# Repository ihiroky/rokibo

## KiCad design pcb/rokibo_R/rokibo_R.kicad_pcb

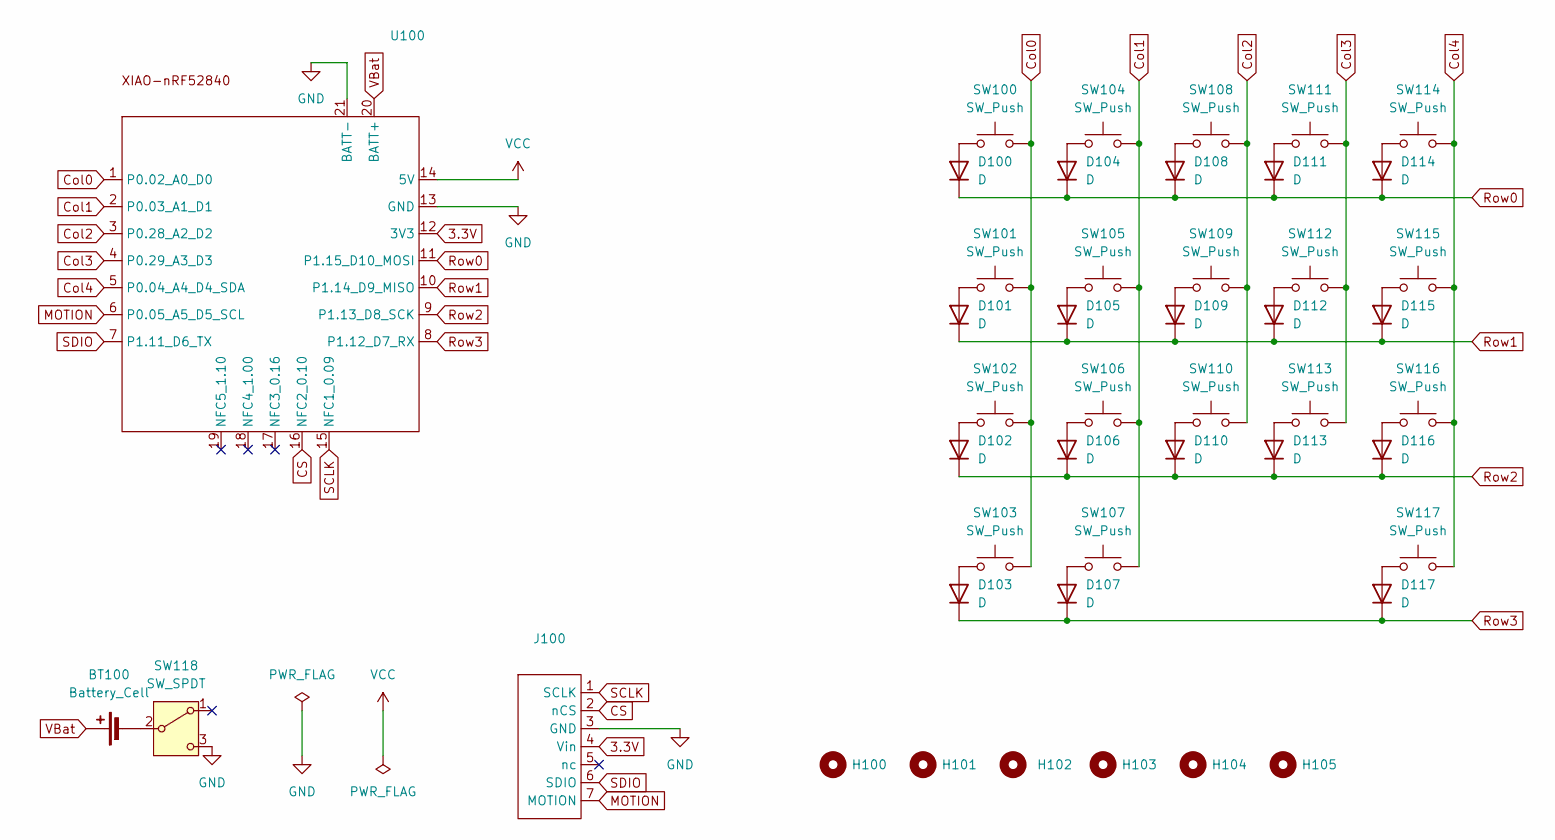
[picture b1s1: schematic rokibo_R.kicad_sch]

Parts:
BT100: Battery_Cell; JST_S2B-PH-SM4-TB
D100, D101, D102, D103, D104, D105, D106, D107, D108, D109, D110, D111, D112, D113, D114, D115, D116, D117: D; Diode_SMD
H100, H101, H102, H103, H104, H105: m2_Spacer_Hole
J100: pmw3610_connector
SW100, SW101, SW102, SW103, SW104, SW105, SW106, SW107, SW108, SW109, SW110, SW111, SW112, SW113, SW114, SW115, SW116, SW117: SW_Push; SW_MX_Choc_THCS
SW118: SW_SPDT; TGSW_MSK-12D19
U100: XIAO_nRF52840_wBAT_wNFC_1

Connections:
3.3V: J100.4 (Vin), U100.12 (3V3)
CS: J100.2 (nCS), U100.16 (NFC2_0.10)
Col0: SW100.2, SW101.2, SW102.2, SW103.2, U100.1 (P0.02_A0_D0)
Col1: SW104.2, SW105.2, SW106.2, SW107.2, U100.2 (P0.03_A1_D1)
Col2: SW108.2, SW109.2, SW110.2, U100.3 (P0.28_A2_D2)
Col3: SW111.2, SW112.2, SW113.2, U100.4 (P0.29_A3_D3)
Col4: SW114.2, SW115.2, SW116.2, SW117.2, U100.5 (P0.04_A4_D4_SDA)
GND: J100.3 (GND), SW118.3 (C), U100.13 (GND), U100.21 (BATT-)
MOTION: J100.7 (MOTION), U100.6 (P0.05_A5_D5_SCL)
unnamed: BT100.2 (-), SW118.2 (B)
unnamed: D100.2 (A), SW100.1
unnamed: D101.2 (A), SW101.1
unnamed: D102.2 (A), SW102.1
unnamed: D103.2 (A), SW103.1
unnamed: D104.2 (A), SW104.1
unnamed: D105.2 (A), SW105.1
unnamed: D106.2 (A), SW106.1
unnamed: D107.2 (A), SW107.1
unnamed: D108.2 (A), SW108.1
unnamed: D109.2 (A), SW109.1
unnamed: D110.2 (A), SW110.1
unnamed: D111.2 (A), SW111.1
unnamed: D112.2 (A), SW112.1
unnamed: D113.2 (A), SW113.1
unnamed: D114.2 (A), SW114.1
unnamed: D115.2 (A), SW115.1
unnamed: D116.2 (A), SW116.1
unnamed: D117.2 (A), SW117.1
Row0: D100.1 (K), D104.1 (K), D108.1 (K), D111.1 (K), D114.1 (K), U100.11 (P1.15_D10_MOSI)
Row1: D101.1 (K), D105.1 (K), D109.1 (K), D112.1 (K), D115.1 (K), U100.10 (P1.14_D9_MISO)
Row2: D102.1 (K), D106.1 (K), D110.1 (K), D113.1 (K), D116.1 (K), U100.9 (P1.13_D8_SCK)
Row3: D103.1 (K), D107.1 (K), D117.1 (K), U100.8 (P1.12_D7_RX)
SCLK: J100.1 (SCLK), U100.15 (NFC1_0.09)
SDIO: J100.6 (SDIO), U100.7 (P1.11_D6_TX)
VBat: BT100.1 (+), U100.20 (BATT+)
VCC: U100.14 (5V)

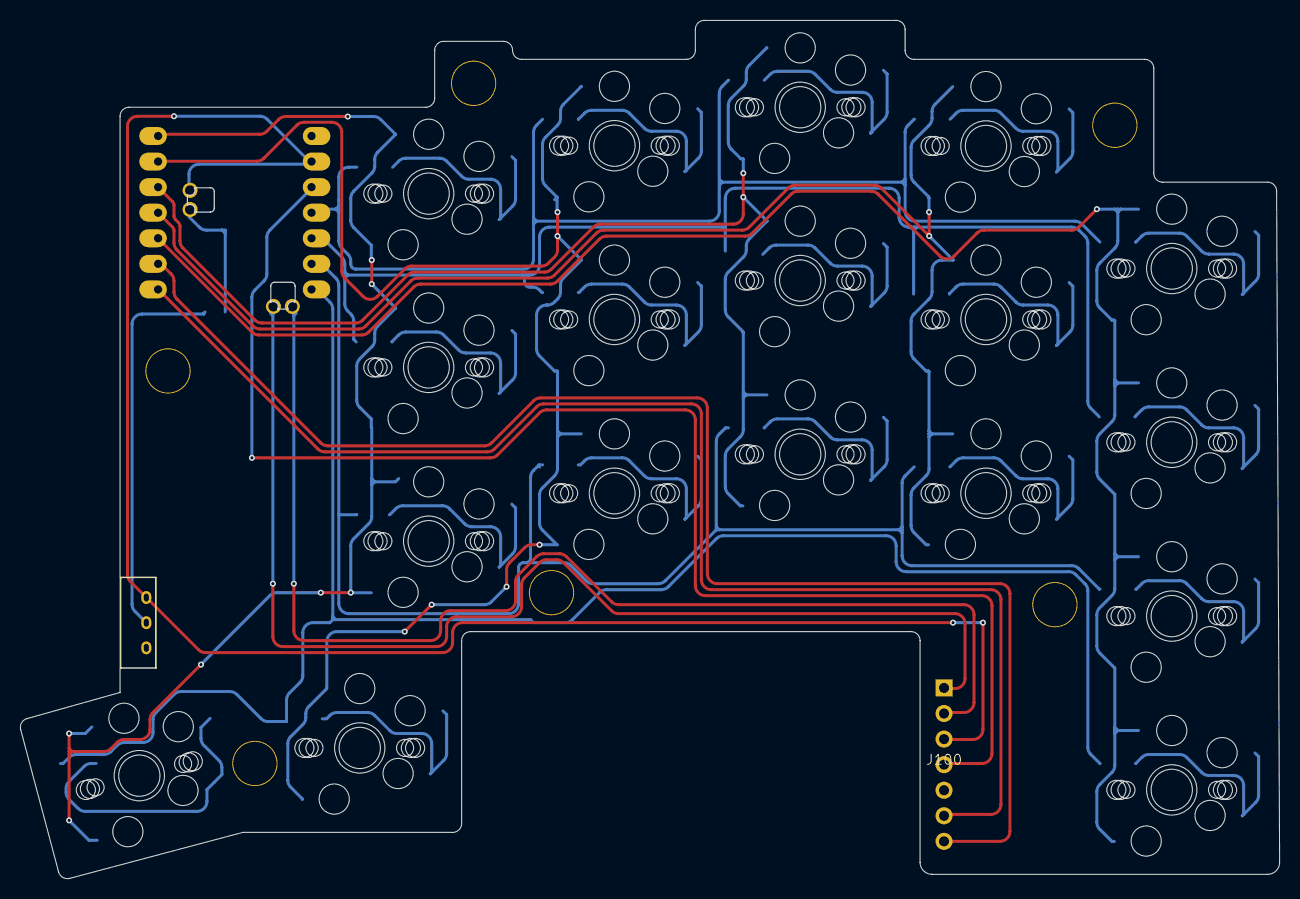
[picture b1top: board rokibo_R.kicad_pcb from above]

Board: 2 copper layers, 125.0 x 85.2 mm, 46 parts (1 on the bottom side), 35 nets.

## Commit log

2026-02-23 Initial commit:
2026-02-23 chore: Add README and .gitignore
2026-03-01 chore: Add parts list
2026-03-01 fix: Draw symmetric edge cut
2026-03-01 feat: Add right side pcb
2026-03-08 feat: Draw left track
2026-03-08 fix: Use XIAO BLE footprint with hole
2026-03-15 feat: Add library for this project
2026-03-15 fix: Update tracks
2026-03-15 chore: Update parts list
